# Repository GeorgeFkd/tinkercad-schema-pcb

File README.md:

# electronics-product-development
Project that includes the tinkercad implementation, the schema and the final pcb

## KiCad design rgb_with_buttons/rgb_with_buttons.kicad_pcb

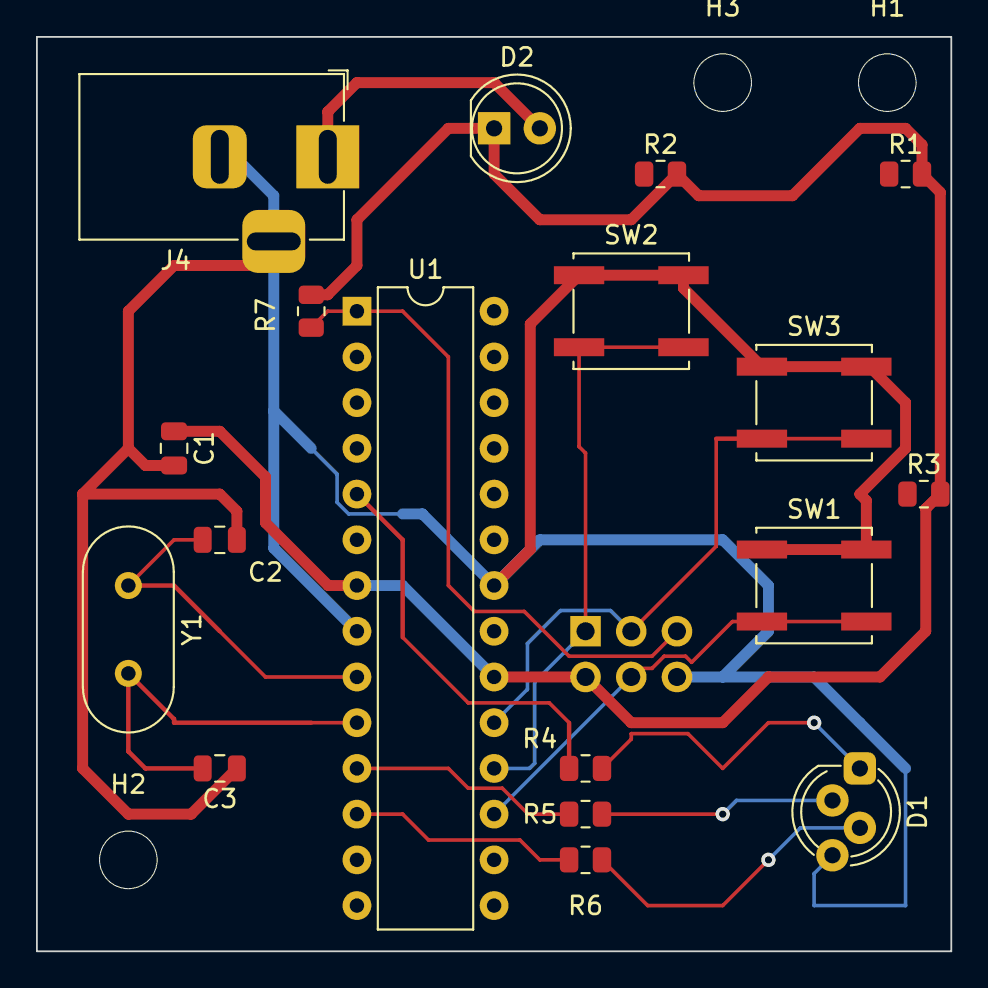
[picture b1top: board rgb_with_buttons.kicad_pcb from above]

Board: 2 copper layers, 50.8 x 50.8 mm, 22 parts (1 on the bottom side), 15 nets.

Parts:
C1, C2, C3: C; C_0805_2012Metric
D1: LED_RGBA; LED_D5.0mm-4_RGB_Staggered_Pins
D2: LED; LED_D5.0mm
H1, H2, H3: MountingHole; MountingHole_3.2mm_M3
J1: ISP; PinHeader_2x03_P2.54mm_Vertical
J4: Barrel_Jack_Switch; BarrelJack_Horizontal
R1: 10KΩ; R_0805_2012Metric
R2, R3, R4, R5, R6, R7: R; R_0805_2012Metric
SW1, SW2, SW3: SW_MEC_5E; SW_Push_1P1T_NO_CK_KSC6xxJ
U1: ATmega328P-P; DIP-28_W7.62mm
Y1: Crystal; Crystal_HC49-4H_Vertical

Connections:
/3: R4.1, U1.5 (PD3)
/5: R5.1, U1.11 (PD5)
/6: R6.1, U1.12 (PD6)
/MISO: J1.1, SW2.1 (b1), U1.18 (PB4)
/MOSI: J1.4, SW1.1 (b1), U1.17 (PB3)
/RESET: J1.5, R7.2, U1.1 (~RESET/PC6)
/SCK: J1.3, SW3.1 (b1), U1.19 (PB5)
/XTAL1: C2.2, U1.9 (XTAL1/PB6), Y1.1
/XTAL2: C3.2, U1.10 (XTAL2/PB7), Y1.2
GND: C1.2, C2.1, C3.1, D1.4 (A), J1.6, J4.2, J4.3, SW1.2 (a2), SW2.2 (a2), SW3.2 (a2), U1.8 (GND), U1.22 (GND)
unnamed: D1.1 (RK), R4.2
unnamed: D1.2 (GK), R5.2
unnamed: D1.3 (BK), R6.2
unnamed: D2.2 (A), J4.1
VCC: C1.1, D2.1 (K), J1.2, R1.2, R2.2, R3.2, R7.1, U1.7 (VCC), U1.20 (AVCC)

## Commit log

2022-12-21 first commit, pcb not yet finished
2022-12-23 all pcb is ready, not quite beautiful but functioning
2022-12-23 pcb is now complete(only warnings in DRC due to problem of the led design), had to change the symbol of the button a bit(nothing significant pin numbers only)
2022-12-23 uploaded image along with a pdf with the proper black background
